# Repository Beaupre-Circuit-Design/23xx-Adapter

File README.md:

# 23xx Adapter

# Introduction

This is a rework of the excellent design made by Jim Brain to replace a 23xx ROM with a standard JEDEC 28 or 32 pin EPROM/EEPROM or Flash ROM. The main difference, this version is 1.9mm smaller in width and more centered on the socket, allowing enough spacing to replace all three roms in a C64 long-board version where Jim's is a little bit too large to install two side by side.

Since 23xx ROMs can be produced with active high or low select lines, the adapter can decode theses signals and select the ROM on the right one. Also the highest address lines not used by the original ROM are available via SMT pads for permanent configuration, or headers to allow bank dynamic bank switching.

# Configuration

The onboard 74HCT138 3-to-8 decoder converts any combination of the 3 possible chip select lines into a single JEDEC standard select line.  If a select line is not needed, that input can be tied to ground via SMT pads on the bottom of the PCB.

|Pad|Position|                                                                      |
|---|--------|----------------------------------------------------------------------|
|18 |1-2     |Line is routed to adress line A11, SMT Pad A should be solder close   |
|18 |2-3     |Line is used as chip select, A11 can be drive by the SMT Pad or header|
|20 |1-2     |Line is routed to <span style="text-decoration:overline">OE</span>    |
|20 |2-3     |Line is used as chip select                                           |
|21 |1-2     |Line is routed to adress line A12, SMT Pad C should be solder close   |
|20 |2-3     |Line is used as chip select, A12 can be drive by the SMT Pad or header|

Once configured, the following truth table show all the possible output at SMT Pads 0-7, solder the pad that is low when the original chip is selected.

|18|20|21|0|1|2|3|4|5|6|7|
|--|--|--|-|-|-|-|-|-|-|-|
|L |L |L |L|H|H|H|H|H|H|H|
|H |L |L |H|L|H|H|H|H|H|H|
|L |H |L |H|H|L|H|H|H|H|H|
|H |H |L |H|H|H|L|H|H|H|H|
|L |L |H |H|H|H|H|L|H|H|H|
|H |L |H |H|H|H|H|H|L|H|H|
|L |H |H |H|H|H|H|H|H|L|H|
|H |H |H |H|H|H|H|H|H|H|L|

## Configuration example for common ICs

|IC Model|Notes                        |A|B|C|18 |20 |21 |0|1|2|3|4|5|6|7||
|--------|-----------------------------|:-:|:-:|:-:|:-:|:-:|:-:|:-:|:-:|:-:|:-:|:-:|:-:|:-:|:-:|:-:|
|2316    |!CS1, !CS2, CS3              | | | |2-3|2-3|2-3| | | | |X| | | ||
|2716    |!EP, !G, Vpp                 | | | |2-3|2-3|2-3| | | | |X| | | ||
|2332    |!CS1, CS2                    |X| | |1-2|2-3|2-3| | | | |X| | | ||
|2364    |!CS1                         |X| |X|1-2|2-3|1-2|X| | | | | | | ||
|2364    |!CS1</br>(Alt, no 74LS138 decoding)| | | |1-2|1-2|1-2| | | | | | | | ||
|2364    |CS1                          |X| |X|1-2|2-3|1-2| | |X| | | | | ||

## Notes if using EEPROM
Do not forget to pull-up the <span style="text-decoration:overline">WE</span> pin or you risk overwriting your EEPROM. As example if using a 28C64/256, solder pad A14, or for 28C512/010/040, solder pad A18.

## Rom banking

Depending on the size of the original and replacement rom, address lines 11 to 18 are available for bank switching, eiter by solder pads or using the 1.27mm header as shown in the pictures below.

|Solder Pads|1.27mm Header|
|:---------:|:-----------:|
|||

# Components and assembly

[Gerbers files](Gerbers/) and SMD assembly files are available for uploading to your prefered manufacturer (I personnally use JLCPCB).  The PCB use SMT parts, except for the headers) while the control board use through-hole components. Refer to the [Bill of Materials](23xx_Adapter_Bom.xlsx) Excel sheet for a complete list of needed components.

# Licence

This work is licensed under the Creative Commons Attribution-NonCommercial-ShareAlike 4.0 International License. To view a copy of this license, visit http://creativecommons.org/licenses/by-nc-sa/4.0/ or send a letter to Creative Commons, PO Box 1866, Mountain View, CA 94042, USA.

# Revision History

|Revision  |Description                    |
|:--------:|-------------------------------|
|1.0       |Initial prototype              |
|2.0       |Add bank switching header      |

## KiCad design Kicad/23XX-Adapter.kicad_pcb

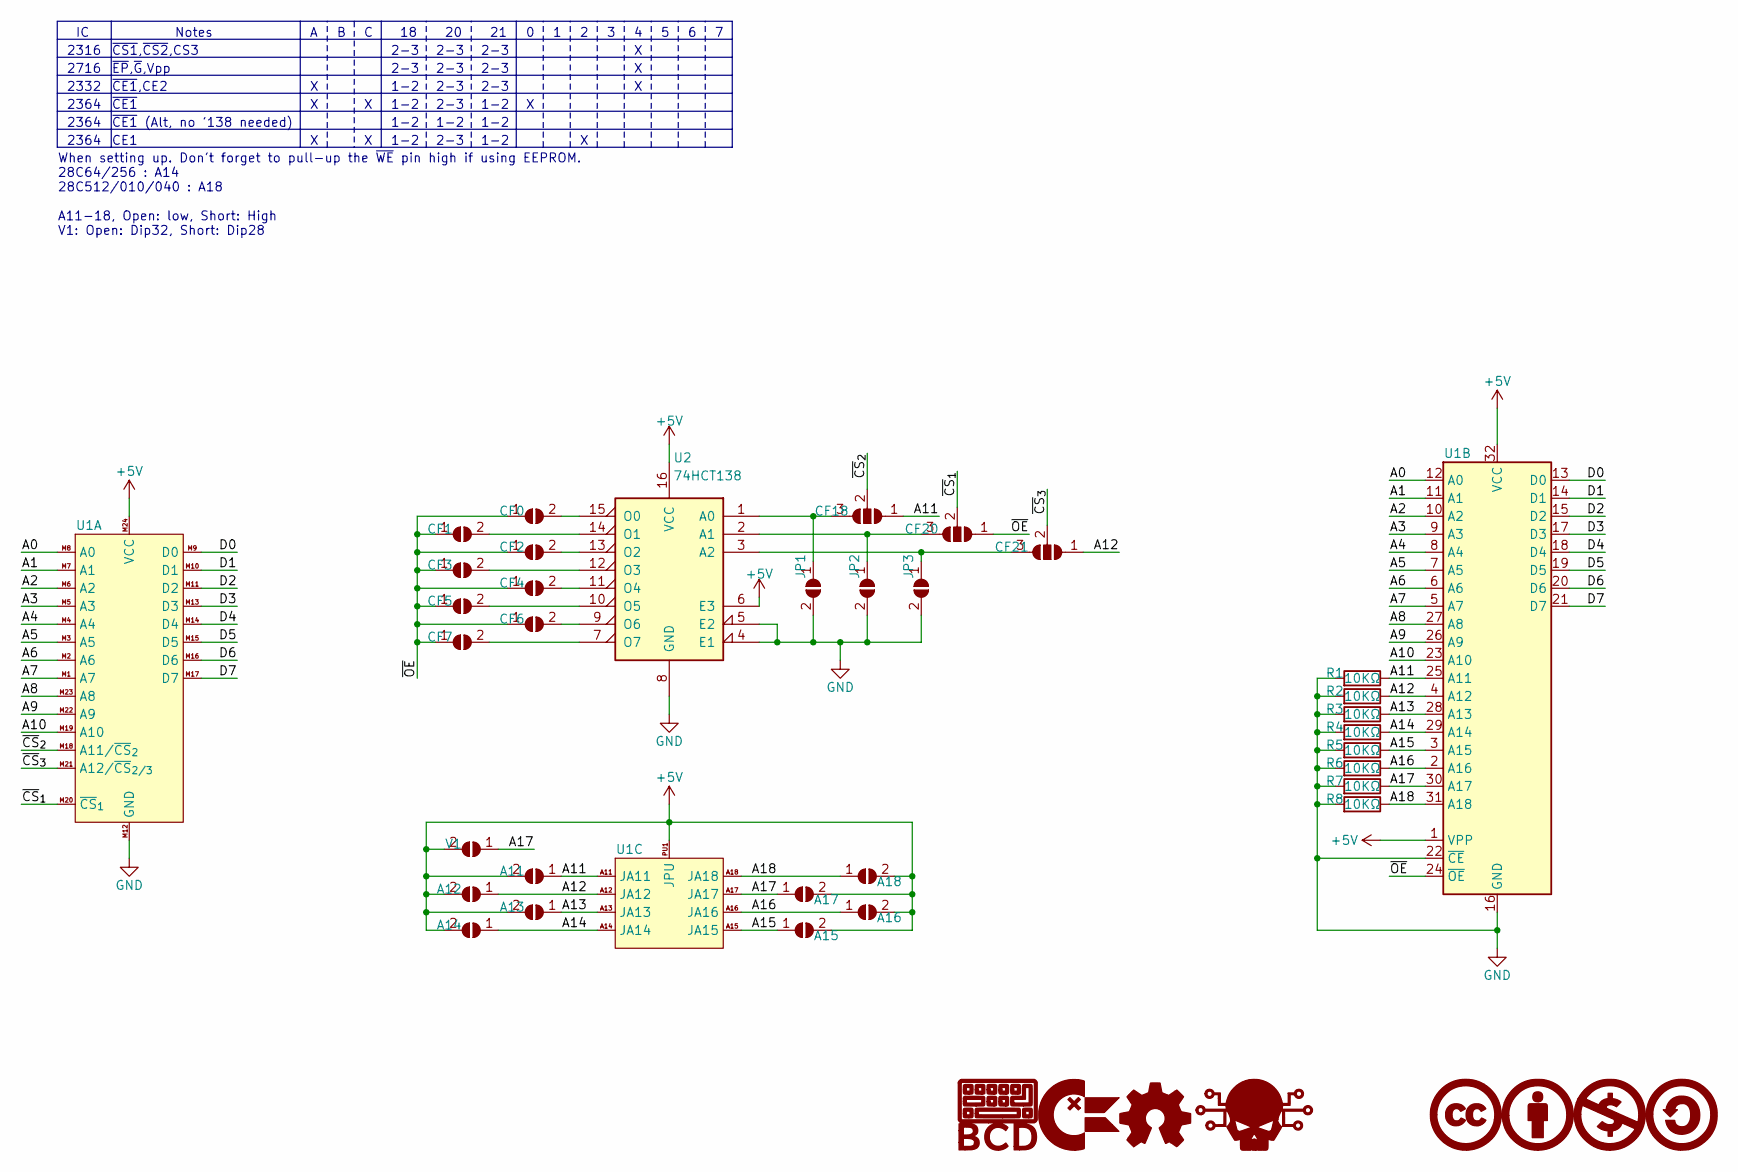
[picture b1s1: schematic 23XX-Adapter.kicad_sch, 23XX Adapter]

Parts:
A11, A12, A13, A14, A15, A16, A17, A18: SolderJumper_2_Open; SolderJumper-2_P1.3mm_Open_RoundedPad1.0x1.5mm
CF0, CF1, CF2, CF3, CF4, CF5, CF6, CF7: SolderJumper_2_Open; SolderJumper-2_P1.3mm_Open_RoundedPad1.0x1.5mm
CF18, CF20, CF21: SolderJumper_3_Open; SolderJumper-3_P1.3mm_Open_RoundedPad1.0x1.5mm_NumberLabels
G1: BCD_Logo; BCD_Logo_5mm
G2: ChickenLips; ChickenLips_2.5mm
G3: OpenSource_Hardware; Open_Source_Hardware_2.5mm
G4: CreativeCommons; CreativeCommons_2.5mm
G5: CreativeCommons_NonCommercial; CreativeCommons_NonCommercial_2.5mm
G6: CreativeCommons_Attribution; CreativeCommons_Attribution_2.5mm
G7: CreativeCommons_ShareAlike; CreativeCommons_ShareAlike_2.5mm
G8: Skull; Skull_2.5mm
JP1, JP2, JP3: SolderJumper_2_Open; SolderJumper-2_P1.3mm_Open_RoundedPad1.0x1.5mm
R1, R2, R3, R4, R5, R6, R7, R8: 10KΩ; R_0603_1608Metric; Mfr.Part 0603WAF1002T5E; LCSC C25804
U1: MOS_23xx_to_27xxx
U2: 74HCT138; SOIC-16_3.9x9.9mm_P1.27mm; Mfr.Part SN74HCT138DR; LCSC C352958
V1: SolderJumper_2_Open; SolderJumper-2_P1.3mm_Open_RoundedPad1.0x1.5mm

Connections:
+5V: A11.2 (B), A12.2 (B), A13.2 (B), A14.2 (B), A15.2 (B), A16.2 (B), A17.2 (B), A18.2 (B), U1.1 (VPP), U1.32 (VCC), U1.M24 (VCC), U1.PU1 (JPU), U2.6 (E3), U2.16 (VCC), V1.2 (B)
/A0: U1.12 (A0), U1.M8 (A0)
/A1: U1.11 (A1), U1.M7 (A1)
/A2: U1.10 (A2), U1.M6 (A2)
/A3: U1.9 (A3), U1.M5 (A3)
/A4: U1.8 (A4), U1.M4 (A4)
/A5: U1.7 (A5), U1.M3 (A5)
/A6: U1.6 (A6), U1.M2 (A6)
/A7: U1.5 (A7), U1.M1 (A7)
/A8: U1.27 (A8), U1.M23 (A8)
/A9: U1.26 (A9), U1.M22 (A9)
/A10: U1.23 (A10), U1.M19 (A10)
/A11: A11.1 (A), CF18.1 (A), R1.1, U1.25 (A11), U1.A11 (JA11)
/A12: A12.1 (A), CF21.1 (A), R2.1, U1.4 (A12), U1.A12 (JA12)
/A13: A13.1 (A), R3.1, U1.28 (A13), U1.A13 (JA13)
/A14: A14.1 (A), R4.1, U1.29 (A14), U1.A14 (JA14)
/A15: A15.1 (A), R5.1, U1.3 (A15), U1.A15 (JA15)
/A16: A16.1 (A), R6.1, U1.2 (A16), U1.A16 (JA16)
/A17: A17.1 (A), R7.1, U1.30 (A17), U1.A17 (JA17), V1.1 (A)
/A18: A18.1 (A), R8.1, U1.31 (A18), U1.A18 (JA18)
/D0: U1.13 (D0), U1.M9 (D0)
/D1: U1.14 (D1), U1.M10 (D1)
/D2: U1.15 (D2), U1.M11 (D2)
/D3: U1.17 (D3), U1.M13 (D3)
/D4: U1.18 (D4), U1.M14 (D4)
/D5: U1.19 (D5), U1.M15 (D5)
/D6: U1.20 (D6), U1.M16 (D6)
/D7: U1.21 (D7), U1.M17 (D7)
/~CS_{1}: CF20.2 (C), U1.M20 (~CS_{1})
/~CS_{2}: CF18.2 (C), U1.M18 (A11/~CS_{2})
/~CS_{3}: CF21.2 (C), U1.M21 (A12/~CS_{2/3})
/~OE: CF0.1 (A), CF1.1 (A), CF2.1 (A), CF3.1 (A), CF4.1 (A), CF5.1 (A), CF6.1 (A), CF7.1 (A), CF20.1 (A), U1.24 (~OE)
GND: JP1.2 (B), JP2.2 (B), JP3.2 (B), R1.2, R2.2, R3.2, R4.2, R5.2, R6.2, R7.2, R8.2, U1.16 (GND), U1.22 (~CE), U1.M12 (GND), U2.4 (E1), U2.5 (E2), U2.8 (GND)
unnamed: CF0.2 (B), U2.15 (O0)
unnamed: CF1.2 (B), U2.14 (O1)
unnamed: CF2.2 (B), U2.13 (O2)
unnamed: CF3.2 (B), U2.12 (O3)
unnamed: CF4.2 (B), U2.11 (O4)
unnamed: CF5.2 (B), U2.10 (O5)
unnamed: CF6.2 (B), U2.9 (O6)
unnamed: CF7.2 (B), U2.7 (O7)
unnamed: CF18.3 (B), JP1.1 (A), U2.1 (A0)
unnamed: CF20.3 (B), JP2.1 (A), U2.2 (A1)
unnamed: CF21.3 (B), JP3.1 (A), U2.3 (A2)

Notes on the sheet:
1-2
2316
~{CS1},~{CS2},CS3
2-3
~{CE1}
~{EP},~{G},Vpp
CE1
2332
~{CE1},CE2
2364
When setting up. Don't forget to pull-up the ~{WE} pin high if using EEPROM. 28C64/256 : A14 28C512/010/040 : A18 A11-18, Open: low, Short: High V1: Open: Dip32, Short: Dip28
~{CE1} (Alt, no '138 needed)
Notes
2716

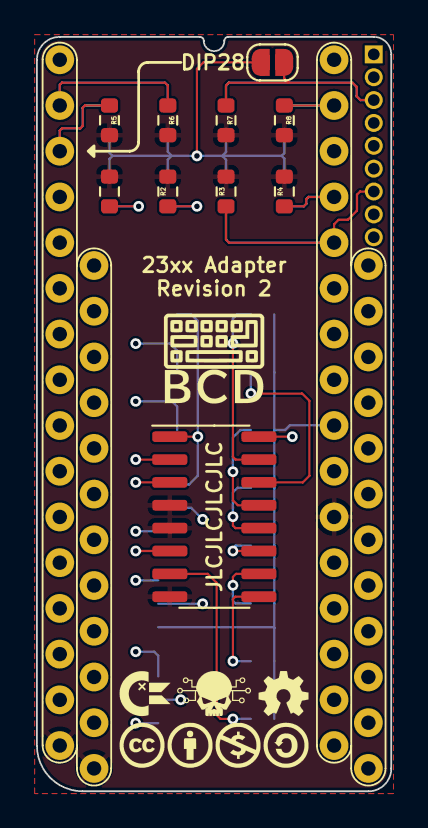
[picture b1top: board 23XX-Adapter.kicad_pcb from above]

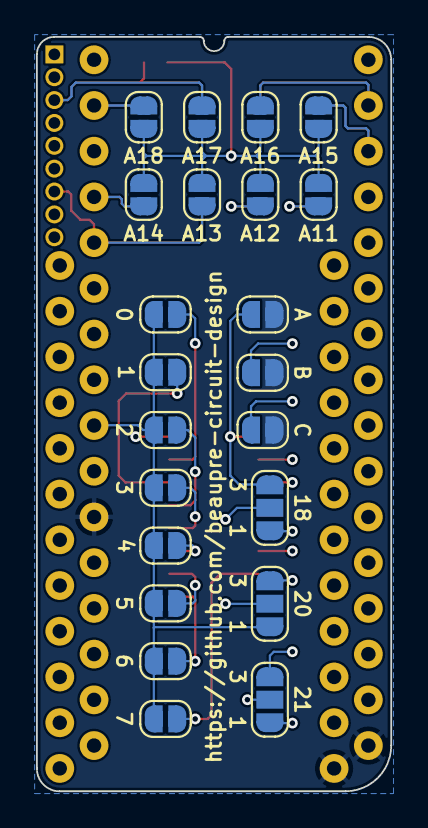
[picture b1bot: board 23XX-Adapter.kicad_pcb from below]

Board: 4 copper layers, 19.7 x 41.9 mm, 41 parts (22 on the bottom side), 44 nets.

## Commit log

2022-03-24 Cleanup
